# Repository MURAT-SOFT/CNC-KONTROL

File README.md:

# CNC-KONTROL
CNC MAKİNESİ KONTROL KARTI STM32F407ZGT6 ARM CORTEX M4 DİZAYN MURAT IRKAN 2022-08-((AUTODESK EAGLE DEVRE TASARIM PROGRAMI)      
https://www.st.com/en/applications/industrial-tools-motor-drives-and-equipment/computer-numerical-control-cnc.html

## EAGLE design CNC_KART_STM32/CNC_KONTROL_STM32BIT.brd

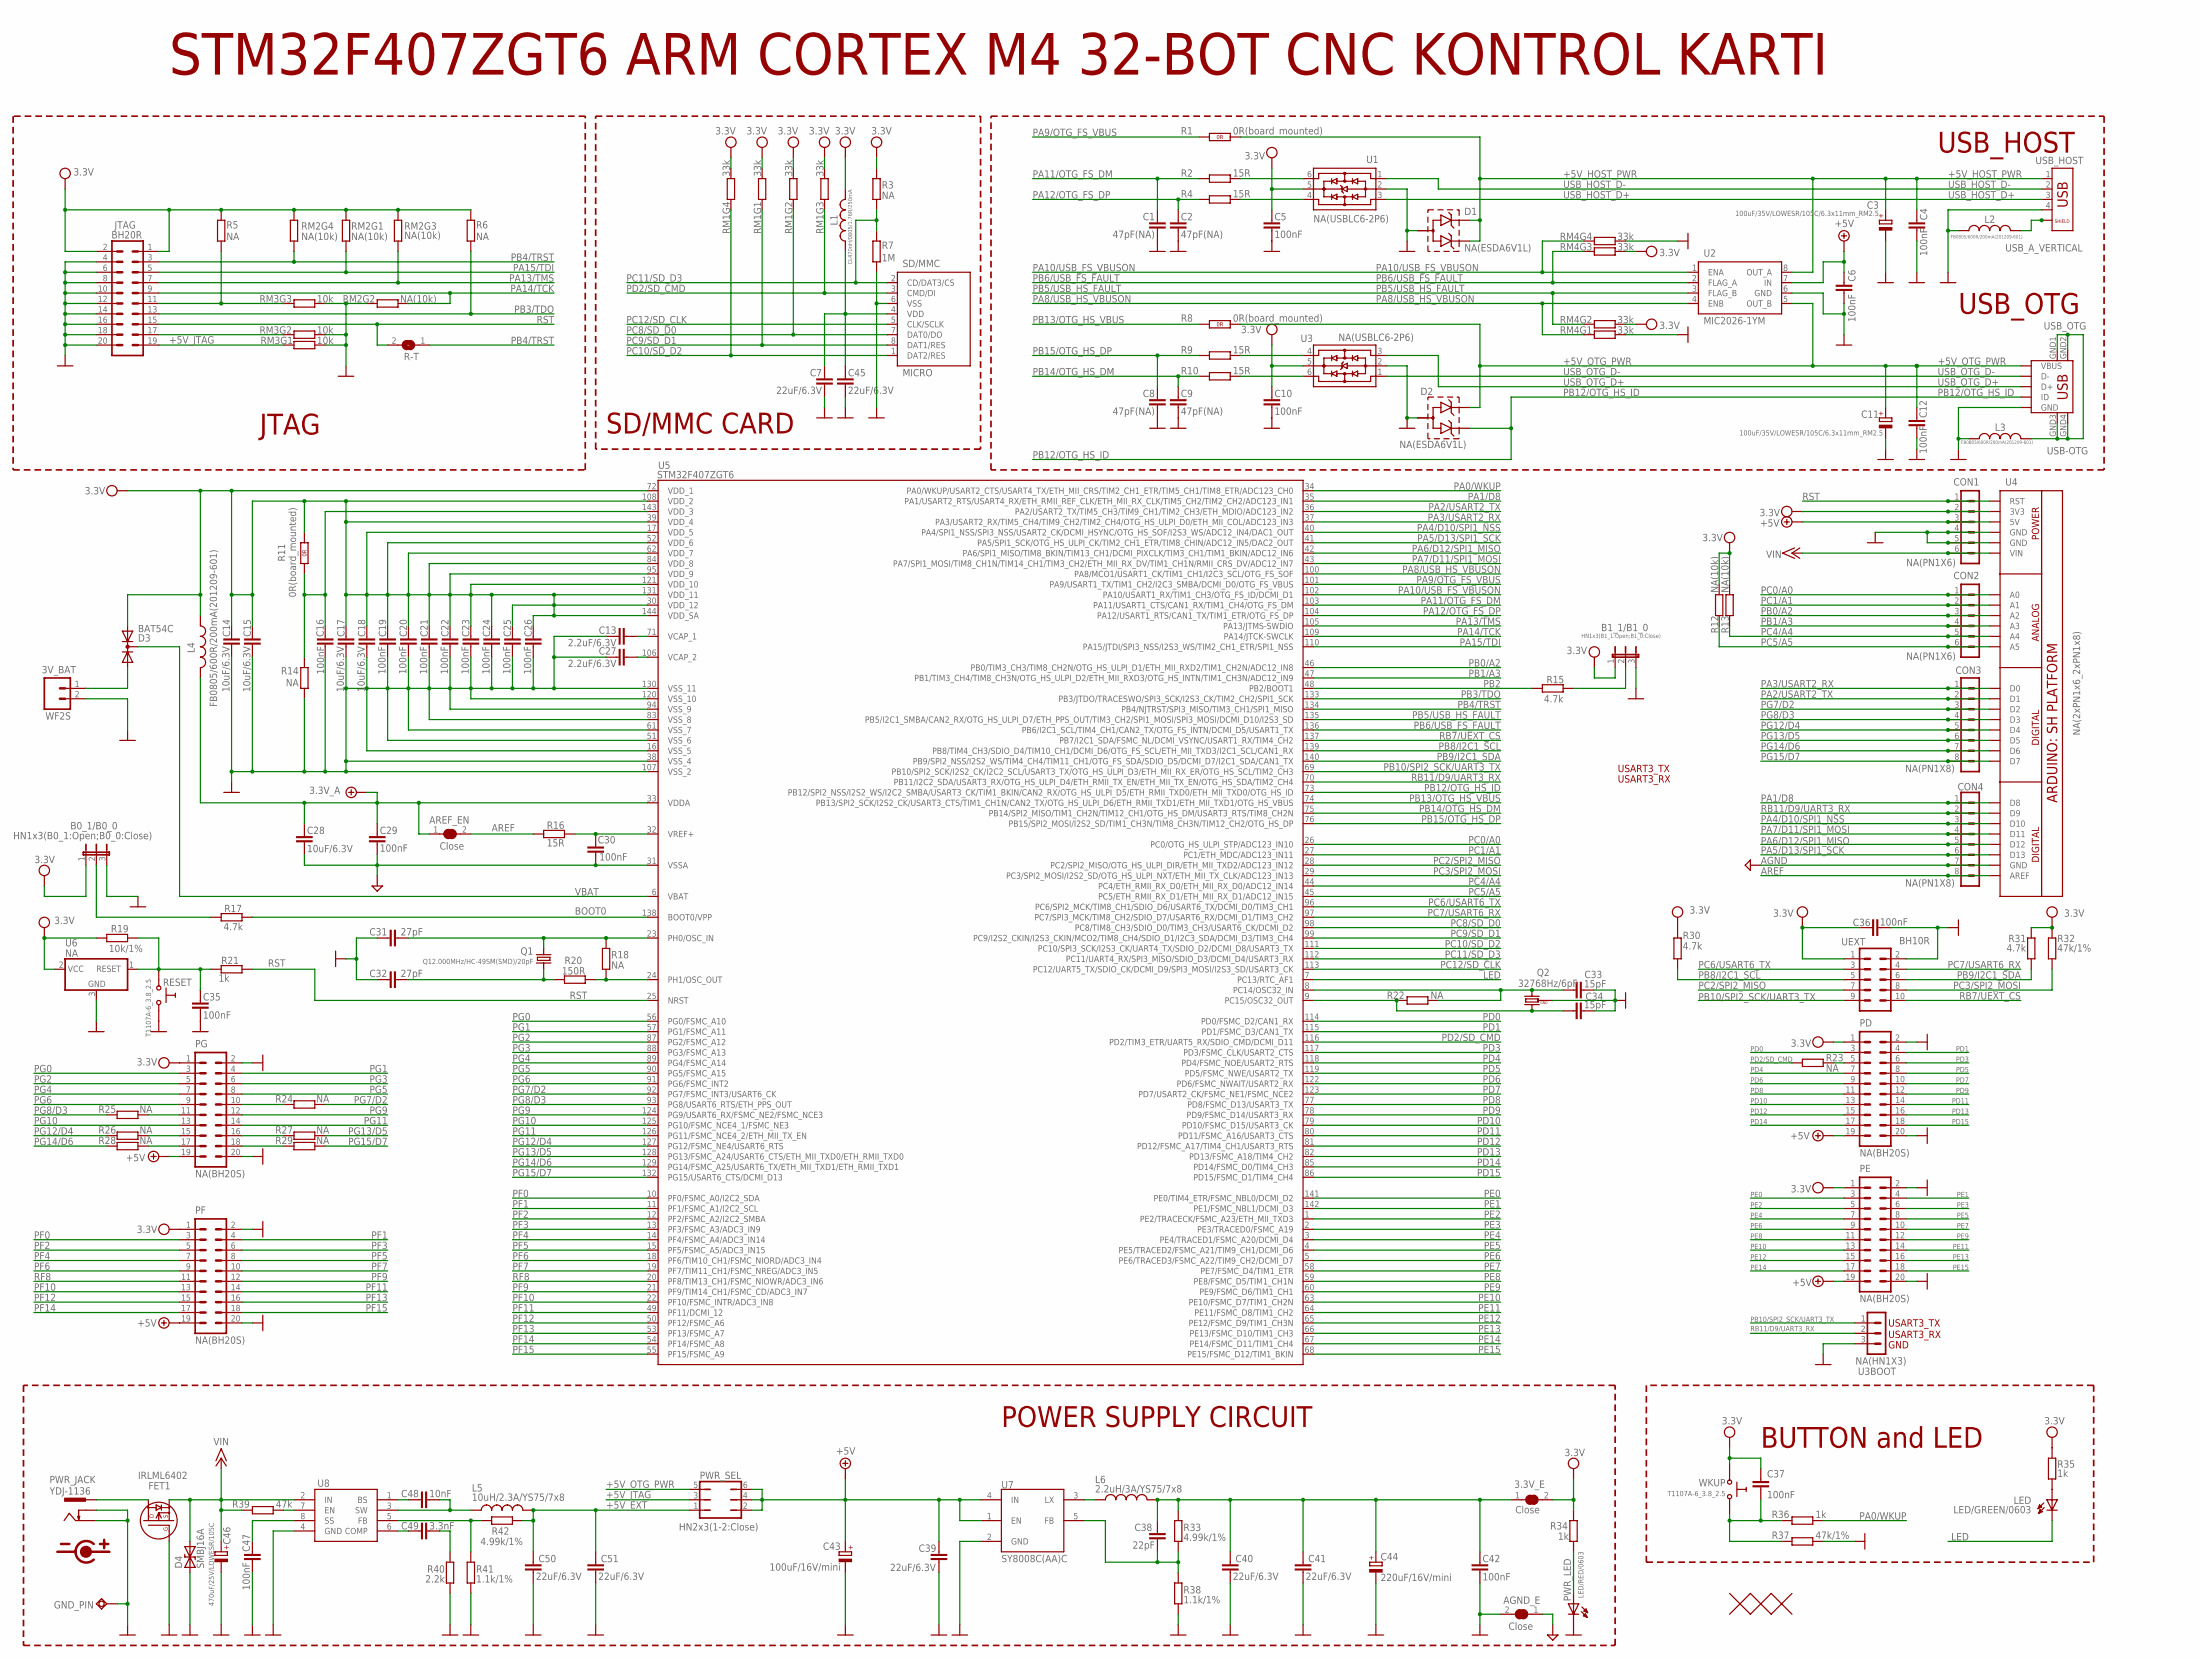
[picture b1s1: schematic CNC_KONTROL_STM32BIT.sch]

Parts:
3.3V_E: Close; SJ_1_SMALLER_CLOSE
3V_BAT: WF2S; CON2.54MM-2-0
AGND_E: Close; SJ_1_SMALLER_CLOSE
AREF_EN: Close; SJ_1_SMALLER_CLOSE
B0_1/B0_0: HN1x3(B0_1:Open;B0_0:Close); JP2
B1_1/B1_0: HN1x3(B1_1:Open;B1_0:Close); JP2
C1, C2, C8, C9: 47pF(NA); C0603_DWS
C3, C11: 100uF/35V/LOWESR/105C/6.3x11mm_RM2.5; E2,5-6,3
C4, C5, C6, C10, C12, C16, C19, C20, C21, C22, C23, C24, C25, C26, C29, C30, C35, C36, C37, C42, C47: 100nF; C0603_DWS
C7, C39, C40, C41, C45, C50, C51: 22uF/6.3V; C0603_DWS
C13, C27: 2.2uF/6.3V; C0603_DWS
C14, C15, C17, C18, C28: 10uF/6.3V; C0603_DWS
C31, C32: 27pF; C0603_DWS
C33, C34: 15pF; C0603_DWS
C38: 22pF; C0603_DWS
C43: 100uF/16V/mini; E2,5-6
C44: 220uF/16V/mini; E3,5-8
C46: 470uF/25V/LOWESR/105C; E5-10,5
C48: 10nF; C0603_DWS
C49: 3.3nF; C0603_DWS
CON1, CON2: NA(PN1X6); PN1X6
CON3, CON4: NA(PN1X8); PN1X8
D1, D2: NA(ESDA6V1L); SOT-23
D3: BAT54C; SOT23C
D4: SMBJ16A; DO214AA
FET1: IRLML6402; SOT23
GND_PIN: TESTPAD3; TEST_PAD40/70/SQUARE
JTAG: BH20R
L1: CL470nH/0805/1.76R/250mA; L0805_5MIL_DWS
L2, L3, L4: FB0805/600R/200mA(201209-601); L0805_5MIL_DWS
L5: 10uH/2.3A/YS75/7x8; L7078
L6: 2.2uH/3A/YS75/7x8; L7078
LED: LED/GREEN/0603; LED-0603
PD: NA(BH20S); ML20-MALE
PE: NA(BH20S); ML20-MALE
PF: NA(BH20S); ML20-MALE
PG: NA(BH20S); ML20-MALE
PWR_JACK: YDJ-1136; PWR_JACK_UNI_MILLING
PWR_LED: LED/RED/0603; LED-0603
PWR_SEL: HN2x3(1-2:Close); JP3Q_NEW
Q1: Q12.000MHz/HC-49SM(SMD)/20pF; HC49/SMD2_THIN
Q2: 32768Hz/6pF; TC26H_3_REPAIR_SMD
R1, R8, R11: 0R(board_mounted); 0603_0R
R2, R4, R9, R10, R16: 15R; R0603_5MIL_DWS
R3, R5, R6, R14, R18, R22, R23: NA; R0603_5MIL_DWS_NA
R7: 1M; R0603_5MIL_DWS
R12, R13: NA(10k); R0603_5MIL_DWS_NA
R15, R17, R30, R31: 4.7k; R0603_5MIL_DWS
R19: 10k/1%; R0603_5MIL_DWS
R20: 150R; R0603_5MIL_DWS
R21, R34, R35, R36: 1k; R0603_5MIL_DWS
R24, R25, R26, R27, R28, R29: NA; R0603_5MIL_DWS
R32, R37: 47k/1%; R0603_5MIL_DWS
R33, R42: 4.99k/1%; R0603_5MIL_DWS
R38, R41: 1.1k/1%; R0603_5MIL_DWS
R39: 47k; R0603_5MIL_DWS
R40: 2.2k; R0603_5MIL_DWS
R-T: Open; SJ_1_SMALLER
RESET: T1107A-6_3.8_2.5; SW-TAKT_6X3.5_SMD
RM1, RM4: 33k; R_MATRIX_4
RM2: NA(10k); R_MATRIX_4
RM3: 10k; R_MATRIX_4
SD/MMC: MICRO; TFR-MEM-CON
U1, U3: NA(USBLC6-2P6); USBLC6-2P6
U2: MIC2026-1YM; SO-8
U3BOOT: NA(HN1X3); HN1X3
U4: NA(2xPN1x6_2xPN1x8); ARDUINO_SHIELD_PLATFORM_WITHOUT_DIMENSION
U5: STM32F407ZGT6; LQFP144
U6: NA; SOT23
U7: SY8008C(AA)C; SOT23-5
U8: MP1482DS; SOIC8
U$1, U$2, U$9: FIDUCIAL1X2; FIDUCIAL-1X2
UEXT: BH10R
USB_HOST: USB_A_VERTICAL; USB_A_VERTICAL_PTH
USB_OTG: USB-OTG; USB_MINI_9PIN
WKUP: T1107A-6_3.8_2.5; SW-TAKT_6X3.5_SMD

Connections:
+5V: C6.1, C39.1, C43.+, CON1.3, PD.19, PE.19, PF.19, PG.19, PWR_SEL.2, PWR_SEL.4, PWR_SEL.6, U2.7 (IN), U4.5V, U7.1 (EN), U7.4 (IN)
+5V_EXT: C50.1, C51.1, L5.2, PWR_SEL.1, R42.2
+5V_HOST_PWR: C3.+, C4.1, D1.1, D1.2, R1.2 (1.2), U2.8 (OUT_A), USB_HOST.1
+5V_JTAG: JTAG.19, PWR_SEL.3, RM3.1.1 (1)
+5V_OTG_PWR: C11.+, C12.1, D2.1, PWR_SEL.5, R8.2 (1.2), U2.5 (OUT_B), USB_OTG.VBUS
+7V: AREF_EN.1, C28.1, C29.2, L4.2, U5.33 (VDDA)
+15V: C46.+, CON1.6, D4.C (2), FET1.2 (S), R39.1, U4.VIN, U8.2 (IN)
AGND: AGND_E.1, C28.2, C29.1, C30.1, CON4.7, U4.GND@2 (GND), U5.31 (VSSA)
AREF: AREF_EN.2, CON4.8, R16.1, U4.AREF
BOOT0: R17.1, U5.138 (BOOT0/VPP)
GND: 3V_BAT.2, AGND_E.2, B0_1/B0_0.3, B1_1/B1_0.3, C1.2, C2.2, C3.-, C4.2, C5.1, C6.2, C7.2, C8.2, C9.2, C10.1, C11.-, C12.2, C13.1, C14.1, C15.1, C16.1, C17.1, C18.1, C19.1, C20.1, C21.1, C22.1, C23.1, C24.1, C25.1, C26.1, C27.1, C31.2, C32.2, C33.2, C34.2, C35.1, C36.1, C39.2, C40.2, C41.2, C42.2, C43.-, C44.-, C45.2, C46.-, C47.2, C50.2, C51.2, CON1.4, CON1.5, D1.3, D2.3, D4.A (1), FET1.1 (G), GND_PIN.P$1, JTAG.4, JTAG.6, JTAG.8, JTAG.10, JTAG.12, JTAG.14, JTAG.16, JTAG.18, JTAG.20, L2.1, L3.1, PD.2, PD.20, PE.2, PE.20, PF.2, PF.20, PG.2, PG.20, PWR_JACK.-, PWR_JACK.--, PWR_LED.C, Q2.GND, R7.2, R14.2, R37.1, R38.2, R40.2, R41.2, RESET.P$2 (1), RM2.2.1 (1), RM3.1.2 (2), RM3.2.2 (2), RM3.3.2 (2), RM4.1.2 (2), RM4.4.2 (2), SD/MMC.6 (VSS), U1.2, U2.6 (GND), U3.2, U3BOOT.3, U4.GND, U4.GND@1 (GND), U5.16 (VSS_5), U5.38 (VSS_4), U5.51 (VSS_6), U5.61 (VSS_7), U5.83 (VSS_8), U5.94 (VSS_9), U5.107 (VSS_2), U5.120 (VSS_10), U5.130 (VSS_11), U6.3 (GND), U7.2 (GND), U8.4 (GND), UEXT.2, USB_HOST.4, USB_OTG.GND
LED: LED.C, U5.7 (PC13/RTC_AF1)
unnamed: C31.1, Q1.2, R18.2, U5.23 (PH0/OSC_IN)
unnamed: C32.1, Q1.1, R20.1
unnamed: R18.1, R20.2, U5.24 (PH1/OSC_OUT)
unnamed: JTAG.17, RM3.2.1 (1)
unnamed: LED.A, R35.1
unnamed: PD.5, R23.2
unnamed: C38.2, R33.2, R38.1, U7.5 (FB)
unnamed: B0_1/B0_0.2, R17.2
unnamed: 3.3V_E.1, C38.1, C40.1, C41.1, C42.1, C44.+, L6.2, R33.1
unnamed: PG.11, R25.1
unnamed: PG.10, R24.2
unnamed: PG.16, R27.2
unnamed: R2.2, U1.6
unnamed: R4.2, U1.4
unnamed: PG.18, R29.2
unnamed: PG.17, R28.1
unnamed: PG.15, R26.1
unnamed: C37.1, R36.1, R37.2, WKUP.P$2 (1)
unnamed: B1_1/B1_0.2, R15.2
unnamed: FET1.3 (D), PWR_JACK.+
unnamed: C47.1, U8.8 (SS)
unnamed: R39.2, U8.7 (EN)
unnamed: R9.2, U3.4
unnamed: R10.2, U3.6
unnamed: C48.1, U8.1 (BS)
unnamed: C48.2, L5.1, U8.3 (SW)
unnamed: C49.1, U8.6 (COMP)
unnamed: C49.2, R40.1
unnamed: R41.1, R42.1, U8.5 (FB)
unnamed: L6.1, U7.3 (LX)
unnamed: 3V_BAT.1, D3.2 (A2)
unnamed: C7.1, C45.1, L1.2, SD/MMC.4 (VDD)
unnamed: JTAG.11, R5.1, RM3.3.1 (1)
unnamed: C13.2, U5.71 (VCAP_1)
unnamed: C27.2, U5.106 (VCAP_2)
unnamed: PWR_LED.A, R34.2
unnamed: C35.2, R19.1, R21.2, RESET.P$1 (0), U6.1 (RESET)
unnamed: L2.2, USB_HOST.P$3 (5), USB_HOST.P$4 (6)
unnamed: C16.2, R11.1 (1.1), R14.1, U5.143 (VDD_3)
PA0/WKUP: R36.2, U5.34 (PA0/WKUP/USART2_CTS/USART4_TX/ETH_MII_C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)
PA1/D8: CON4.1, U4.D8, U5.35 (PA1/USART2_RTS/USART4_RX/ETH_RMII_REF_C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)
PA2/USART2_TX: CON3.2, U4.D1, U5.36 (PA2/USART2_TX/TIM5_CH3/TIM9_CH1/TIM2_CH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)
PA3/USART2_RX: CON3.1, U4.D0, U5.37 (PA3/USART2_RX/TIM5_CH4/TIM9_CH2/TIM2_CH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)
PA4/D10/SPI1_NSS: CON4.3, U4.D10, U5.40 (PA4/SPI1_NSS/SPI3_NSS/USART2_CK/DCMI_HS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)
PA5/D13/SPI1_SCK: CON4.6, U4.D13, U5.41 (PA5/SPI1_SCK/OTG_HS_ULPI_CK/TIM2_CH1_ET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)
PA6/D12/SPI1_MISO: CON4.5, U4.D12, U5.42 (PA6/SPI1_MISO/TIM8_BKIN/TIM13_CH1/DCMI_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)
PA7/D11/SPI1_MOSI: CON4.4, U4.D11, U5.43 (PA7/SPI1_MOSI/TIM8_CH1N/TIM14_CH1/TIM3_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)
PA8/USB_HS_VBUSON: RM4.1.1 (1), U2.4 (ENB), U5.100 (PA8/MCO1/USART1_CK/TIM1_CH1/I2C3_SCL/OT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)
PA9/OTG_FS_VBUS: R1.1 (1.1), U5.101 (PA9/USART1_TX/TIM1_CH2/I2C3_SMBA/DCMI_D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)
PA10/USB_FS_VBUSON: RM4.4.1 (1), U2.1 (ENA), U5.102 (PA10/USART1_RX/TIM1_CH3/OTG_FS_ID/DCMI_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)
PA11/OTG_FS_DM: C1.1, R2.1, U5.103 (PA11/USART1_CTS/CAN1_RX/TIM1_CH4/OTG_FS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)
PA12/OTG_FS_DP: C2.1, R4.1, U5.104 (PA12/USART1_RTS/CAN1_TX/TIM1_ETR/OTG_FS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)
PA13/TMS: JTAG.7, RM2.3.1 (1), U5.105 (PA13/JTMS-SWDIO)
PA14/TCK: JTAG.9, RM2.2.2 (2), U5.109 (PA14/JTCK-SWCLK)
PA15/TDI: JTAG.5, RM2.1.1 (1), U5.110 (PA15/JTDI/SPI3_NSS/I2S3_WS/TIM2_CH1_ETR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)
PB0/A2: CON2.3, U4.A2, U5.46 (PB0/TIM3_CH3/TIM8_CH2N/OTG_HS_ULPI_D1/E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)
PB1/A3: CON2.4, U4.A3, U5.47 (PB1/TIM3_CH4/TIM8_CH3N/OTG_HS_ULPI_D2/E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)
PB2: R15.1, U5.48 (PB2/BOOT1)
PB3/TDO: JTAG.13, R6.1, U5.133 (PB3/JTDO/TRACESWO/SPI3_SCK/I2S3_CK/TIM2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)
PB4/TRST: JTAG.3, R-T.1, RM2.4.1 (1), U5.134 (PB4/NJTRST/SPI3_MISO/TIM3_CH1/SPI1_MISO)
PB5/USB_HS_FAULT: RM4.2.1 (1), U2.3 (FLAG_B), U5.135 (PB5/I2C1_SMBA/CAN2_RX/OTG_HS_ULPI_D7/ET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)
PB6/USB_FS_FAULT: RM4.3.1 (1), U2.2 (FLAG_A), U5.136 (PB6/I2C1_SCL/TIM4_CH1/CAN2_TX/OTG_FS_IN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)
PB8/I2C1_SCL: R30.1, U5.139 (PB8/TIM4_CH3/SDIO_D4/TIM10_CH1/DCMI_D6/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), UEXT.5
PB9/I2C1_SDA: R31.1, U5.140 (PB9/SPI2_NSS/I2S2_WS/TIM4_CH4/TIM11_CH1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), UEXT.6
PB10/SPI2_SCK/UART3_TX: U3BOOT.1, U5.69 (PB10/SPI2_SCK/I2S2_CK/I2C2_SCL/USART3_T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), UEXT.9
PB12/OTG_HS_ID: D2.2, U5.73 (PB12/SPI2_NSS/I2S2_WS/I2C2_SMBA/USART3_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), USB_OTG.ID
PB13/OTG_HS_VBUS: R8.1 (1.1), U5.74 (PB13/SPI2_SCK/I2S2_CK/USART3_CTS/TIM1_C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)
PB14/OTG_HS_DM: C9.1, R10.1, U5.75 (PB14/SPI2_MISO/TIM1_CH2N/TIM12_CH1/OTG_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)
PB15/OTG_HS_DP: C8.1, R9.1, U5.76 (PB15/SPI2_MOSI/I2S2_SD/TIM1_CH3N/TIM8_C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)
PC0/A0: CON2.1, U4.A0, U5.26 (PC0/OTG_HS_ULPI_STP/ADC123_IN10)
PC1/A1: CON2.2, U4.A1, U5.27 (PC1/ETH_MDC/ADC123_IN11)
PC2/SPI2_MISO: U5.28 (PC2/SPI2_MISO/OTG_HS_ULPI_DIR/ETH_MII_T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), UEXT.7
PC3/SPI2_MOSI: R32.1, U5.29 (PC3/SPI2_MOSI/I2S2_SD/OTG_HS_ULPI_NXT/E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), UEXT.8
PC4/A4: CON2.5, R13.1, U4.A4, U5.44 (PC4/ETH_RMII_RX_D0/ETH_MII_RX_D0/ADC12_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)
PC5/A5: CON2.6, R12.1, U4.A5, U5.45 (PC5/ETH_RMII_RX_D1/ETH_MII_RX_D1/ADC12_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)
PC6/USART6_TX: U5.96 (PC6/SPI2_MCK/TIM8_CH1/SDIO_D6/USART6_TX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), UEXT.3
PC7/USART6_RX: U5.97 (PC7/SPI3_MCK/TIM8_CH2/SDIO_D7/USART6_RX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), UEXT.4
PC8/SD_D0: RM1.2.1 (1), SD/MMC.7 (DAT0/DO), U5.98 (PC8/TIM8_CH3/SDIO_D0/TIM3_CH3/USART6_CK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)
PC9/SD_D1: RM1.1.1 (1), SD/MMC.8 (DAT1/RES), U5.99 (PC9/I2S2_CKIN/I2S3_CKIN/MCO2/TIM8_CH4/S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)
PC10/SD_D2: RM1.4.1 (1), SD/MMC.1 (DAT2/RES), U5.111 (PC10/SPI3_SCK/I2S3_CK/UART4_TX/SDIO_D2/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)
PC11/SD_D3: R3.2, R7.1, SD/MMC.2 (CD/DAT3/CS), U5.112 (PC11/UART4_RX/SPI3_MISO/SDIO_D3/DCMI_D4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)
PC12/SD_CLK: SD/MMC.5 (CLK/SCLK), U5.113 (PC12/UART5_TX/SDIO_CK/DCMI_D9/SPI3_MOSI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)
PC14: C33.1, Q2.2, R22.2, U5.8 (PC14/OSC32_IN)
PC15: C34.1, Q2.1, R22.1, U5.9 (PC15/OSC32_OUT)
PD0: PD.3, U5.114 (PD0/FSMC_D2/CAN1_RX)
PD1: PD.4, U5.115 (PD1/FSMC_D3/CAN1_TX)
PD2/SD_CMD: R23.1, RM1.3.1 (1), SD/MMC.3 (CMD/DI), U5.116 (PD2/TIM3_ETR/UART5_RX/SDIO_CMD/DCMI_D11)
PD3: PD.6, U5.117 (PD3/FSMC_CLK/USART2_CTS)
PD4: PD.7, U5.118 (PD4/FSMC_NOE/USART2_RTS)
PD5: PD.8, U5.119 (PD5/FSMC_NWE/USART2_TX)
PD6: PD.9, U5.122 (PD6/FSMC_NWAIT/USART2_RX)
PD7: PD.10, U5.123 (PD7/USART2_CK/FSMC_NE1/FSMC_NCE2)
PD8: PD.11, U5.77 (PD8/FSMC_D13/USART3_TX)
PD9: PD.12, U5.78 (PD9/FSMC_D14/USART3_RX)
PD10: PD.13, U5.79 (PD10/FSMC_D15/USART3_CK)
PD11: PD.14, U5.80 (PD11/FSMC_A16/USART3_CTS)
PD12: PD.15, U5.81 (PD12/FSMC_A17/TIM4_CH1/USART3_RTS)
PD13: PD.16, U5.82 (PD13/FSMC_A18/TIM4_CH2)
PD14: PD.17, U5.85 (PD14/FSMC_D0/TIM4_CH3)
PD15: PD.18, U5.86 (PD15/FSMC_D1/TIM4_CH4)
PE0: PE.3, U5.141 (PE0/TIM4_ETR/FSMC_NBL0/DCMI_D2)
PE1: PE.4, U5.142 (PE1/FSMC_NBL1/DCMI_D3)
PE2: PE.5, U5.1 (PE2/TRACECK/FSMC_A23/ETH_MII_TXD3)
PE3: PE.6, U5.2 (PE3/TRACED0/FSMC_A19)
PE4: PE.7, U5.3 (PE4/TRACED1/FSMC_A20/DCMI_D4)
PE5: PE.8, U5.4 (PE5/TRACED2/FSMC_A21/TIM9_CH1/DCMI_D6)
PE6: PE.9, U5.5 (PE6/TRACED3/FSMC_A22/TIM9_CH2/DCMI_D7)
PE7: PE.10, U5.58 (PE7/FSMC_D4/TIM1_ETR)
PE8: PE.11, U5.59 (PE8/FSMC_D5/TIM1_CH1N)
PE9: PE.12, U5.60 (PE9/FSMC_D6/TIM1_CH1)
PE10: PE.13, U5.63 (PE10/FSMC_D7/TIM1_CH2N)
PE11: PE.14, U5.64 (PE11/FSMC_D8/TIM1_CH2)
PE12: PE.15, U5.65 (PE12/FSMC_D9/TIM1_CH3N)
PE13: PE.16, U5.66 (PE13/FSMC_D10/TIM1_CH3)
PE14: PE.17, U5.67 (PE14/FSMC_D11/TIM1_CH4)
PE15: PE.18, U5.68 (PE15/FSMC_D12/TIM1_BKIN)
PF0: PF.3, U5.10 (PF0/FSMC_A0/I2C2_SDA)
PF1: PF.4, U5.11 (PF1/FSMC_A1/I2C2_SCL)
PF2: PF.5, U5.12 (PF2/FSMC_A2/I2C2_SMBA)
PF3: PF.6, U5.13 (PF3/FSMC_A3/ADC3_IN9)
PF4: PF.7, U5.14 (PF4/FSMC_A4/ADC3_IN14)
PF5: PF.8, U5.15 (PF5/FSMC_A5/ADC3_IN15)
PF6: PF.9, U5.18 (PF6/TIM10_CH1/FSMC_NIORD/ADC3_IN4)
PF7: PF.10, U5.19 (PF7/TIM11_CH1/FSMC_NREG/ADC3_IN5)
PF9: PF.12, U5.21 (PF9/TIM14_CH1/FSMC_CD/ADC3_IN7)
PF10: PF.13, U5.22 (PF10/FSMC_INTR/ADC3_IN8)
PF11: PF.14, U5.49 (PF11/DCMI_12)
PF12: PF.15, U5.50 (PF12/FSMC_A6)
PF13: PF.16, U5.53 (PF13/FSMC_A7)
PF14: PF.17, U5.54 (PF14/FSMC_A8)
PF15: PF.18, U5.55 (PF15/FSMC_A9)
PG0: PG.3, U5.56 (PG0/FSMC_A10)
PG1: PG.4, U5.57 (PG1/FSMC_A11)
PG2: PG.5, U5.87 (PG2/FSMC_A12)
PG3: PG.6, U5.88 (PG3/FSMC_A13)
PG4: PG.7, U5.89 (PG4/FSMC_A14)
PG5: PG.8, U5.90 (PG5/FSMC_A15)
PG6: PG.9, U5.91 (PG6/FSMC_INT2)
PG7/D2: CON3.3, R24.1, U4.D2, U5.92 (PG7/FSMC_INT3/USART6_CK)
PG8/D3: CON3.4, R25.2, U4.D3, U5.93 (PG8/USART6_RTS/ETH_PPS_OUT)
PG9: PG.12, U5.124 (PG9/USART6_RX/FSMC_NE2/FSMC_NCE3)
PG10: PG.13, U5.125 (PG10/FSMC_NCE4_1/FSMC_NE3)
PG11: PG.14, U5.126 (PG11/FSMC_NCE4_2/ETH_MII_TX_EN)
PG12/D4: CON3.5, R26.2, U4.D4, U5.127 (PG12/FSMC_NE4/USART6_RTS)
PG13/D5: CON3.6, R27.1, U4.D5, U5.128 (PG13/FSMC_A24/USART6_CTS/ETH_MII_TXD0/E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)
PG14/D6: CON3.7, R28.2, U4.D6, U5.129 (PG14/FSMC_A25/USART6_TX/ETH_MII_TXD1/ET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)
PG15/D7: CON3.8, R29.1, U4.D7, U5.132 (PG15/USART6_CTS/DCMI_D13)
RB7/UEXT_CS: U5.137 (PB7/I2C1_SDA/FSMC_NL/DCMI_VSYNC/USART1_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), UEXT.10
RB11/D9/UART3_RX: CON4.2, U3BOOT.2, U4.D9, U5.70 (PB11/I2C2_SDA/USART3_RX/OTG_HS_ULPI_D4/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)
RF8: PF.11, U5.20 (PF8/TIM13_CH1/FSMC_NIOWR/ADC3_IN6)
RST: CON1.1, JTAG.15, R21.1, R-T.2, U4.RST, U5.25 (NRST)
USB_HOST_D+: U1.3, USB_HOST.3
USB_HOST_D-: U1.1, USB_HOST.2
USB_OTG_D+: U3.3, USB_OTG.D+
USB_OTG_D-: U3.1, USB_OTG.D-
USB_SHIELD: L3.2, USB_OTG.GND1, USB_OTG.GND2, USB_OTG.GND3, USB_OTG.GND4
VBAT: D3.3 (K), U5.6 (VBAT)
VCC: 3.3V_E.2, B0_1/B0_0.1, B1_1/B1_0.1, C5.2, C10.2, C14.2, C15.2, C17.2, C18.2, C19.2, C20.2, C21.2, C22.2, C23.2, C24.2, C25.2, C26.2, C36.2, C37.2, CON1.2, D3.1 (A1), JTAG.1, JTAG.2, L1.1, L4.1, PD.1, PE.1, PF.1, PG.1, R3.1, R5.2, R6.2, R11.2 (1.2), R12.2, R13.2, R19.2, R30.2, R31.2, R32.2, R34.1, R35.2, RM1.1.2 (2), RM1.2.2 (2), RM1.3.2 (2), RM1.4.2 (2), RM2.1.2 (2), RM2.3.2 (2), RM2.4.2 (2), RM4.2.2 (2), RM4.3.2 (2), U1.5, U3.5, U4.3V3, U5.17 (VDD_5), U5.30 (VDD_12), U5.39 (VDD_4), U5.52 (VDD_6), U5.62 (VDD_7), U5.72 (VDD_1), U5.84 (VDD_8), U5.95 (VDD_9), U5.108 (VDD_2), U5.121 (VDD_10), U5.131 (VDD_11), U5.144 (VDD_SA), U6.2 (VCC), UEXT.1, WKUP.P$1 (0)
VREF+: C30.2, R16.2, U5.32 (VREF+)

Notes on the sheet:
POWER SUPPLY CIRCUIT
BUTTON and LED
JTAG
SD/MMC CARD
USB_HOST
USB_OTG
USART3_TX
USART3_RX
GND
STM32F407ZGT6 ARM CORTEX M4 32-BOT CNC KONTROL KARTI

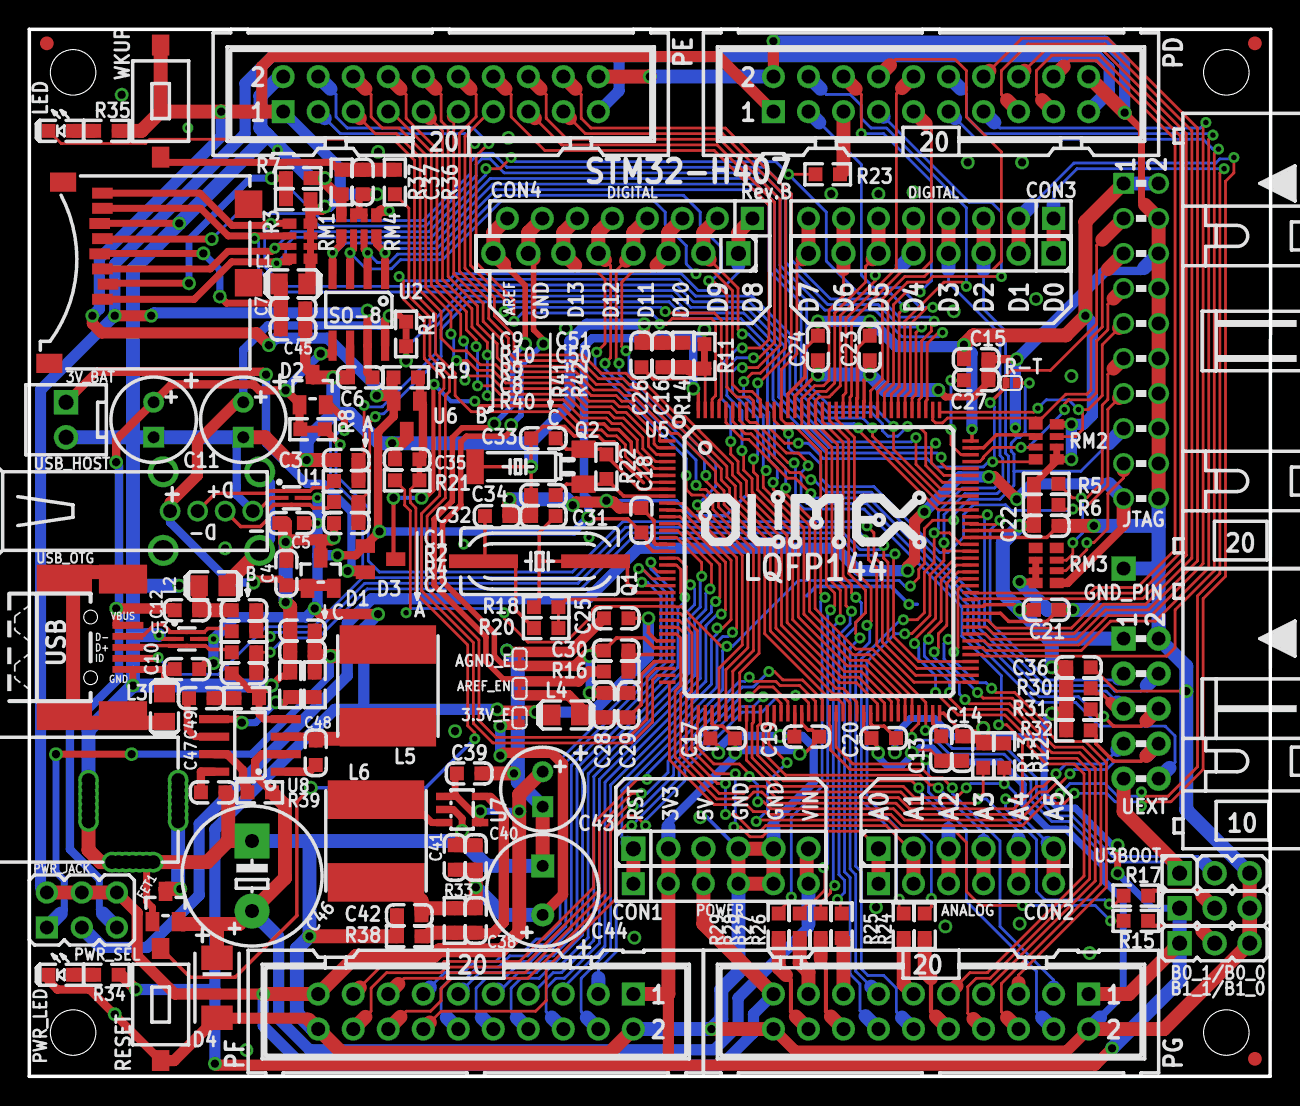
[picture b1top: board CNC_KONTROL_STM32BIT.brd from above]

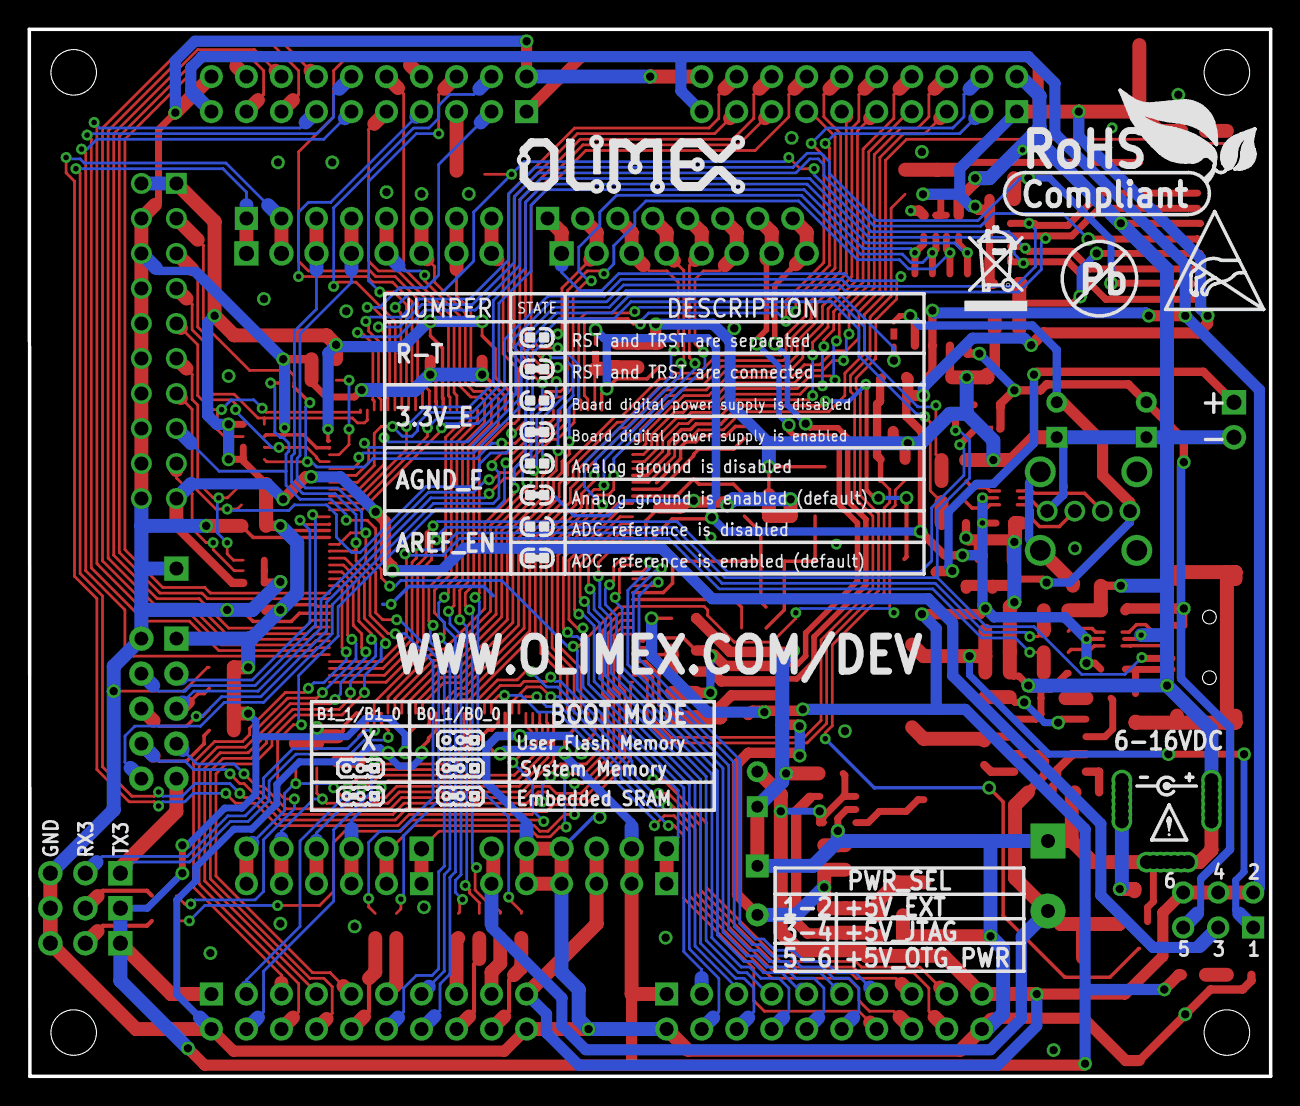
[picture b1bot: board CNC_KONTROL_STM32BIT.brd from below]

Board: 2 copper layers, 90.0 x 75.9 mm, 156 parts (6 on the bottom side), 171 nets.

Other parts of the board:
U$4, U$7: OLIMEX1_V
U$5: ESD_SYMBOL
U$6: PB
U$8: RECYCLE_BIN1/8
U$15: ROHS
U$16: ATTENTION_SMALL

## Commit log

2024-12-12 CNC_KONTROL.md
2024-12-12 CNC MAKİNE KONTROL KARTI (STM32-32BIT ARM CORTEX)
2024-12-12 CNC_BENİOKU.md
2024-12-12 STM32F407 TEKNİK DÖKÜMAN
2024-12-12 CNC_MAKİNE_3D_TASARIM(SOLIDWORKS 2018)
    SOLIDWORKS MİNİ CNC MAKİNE 3D-TASARIM (STEP DOSYASI
